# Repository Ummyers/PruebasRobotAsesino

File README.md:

## PruebasRobotAsesino
El repositorio es para las pruebas del programa final para la competencia de minisumo.

Se esta usando MSP-EXP430G2553 de la fabrica Texas Instruments

Asi como los siguientes componentes: 

1. Un regulador LD33V que convierte 5V a 3.3V el cual usa un condensador #104 (100 nanofaradios) que se conecta entre la entrada del voltaje y GND, un condensador de 10 microfaradios que va de la salida del voltaje a GND. 

2. Un regulador L7805CV que convierte 12V a 5V el cual usa un condensador #104 que va entre la salida y GND, un condensador #334 que es de 330 nanofaradios que se conecta con GND y la entrada de voltaje. 

3. Para controlar los motores usamos un driver L293D, con los pines especificados de la siguiente manera:
   Pines de entrada 2,7,15,10.\\
   Pines de salida 3,6,14,11.
ETC...

Algunas especificaciones del MSP:

El pin 1 es VCC que debe recibir a lo mas 3.3 Volts del pin 1 al 16 va un condensador de 1 nanoFaradio, del pin 16 al 20, una resistencia de 47K.

La fuente inicialmente era de 12V usamos los reguladores para obtener 5 y 3.3 volts.

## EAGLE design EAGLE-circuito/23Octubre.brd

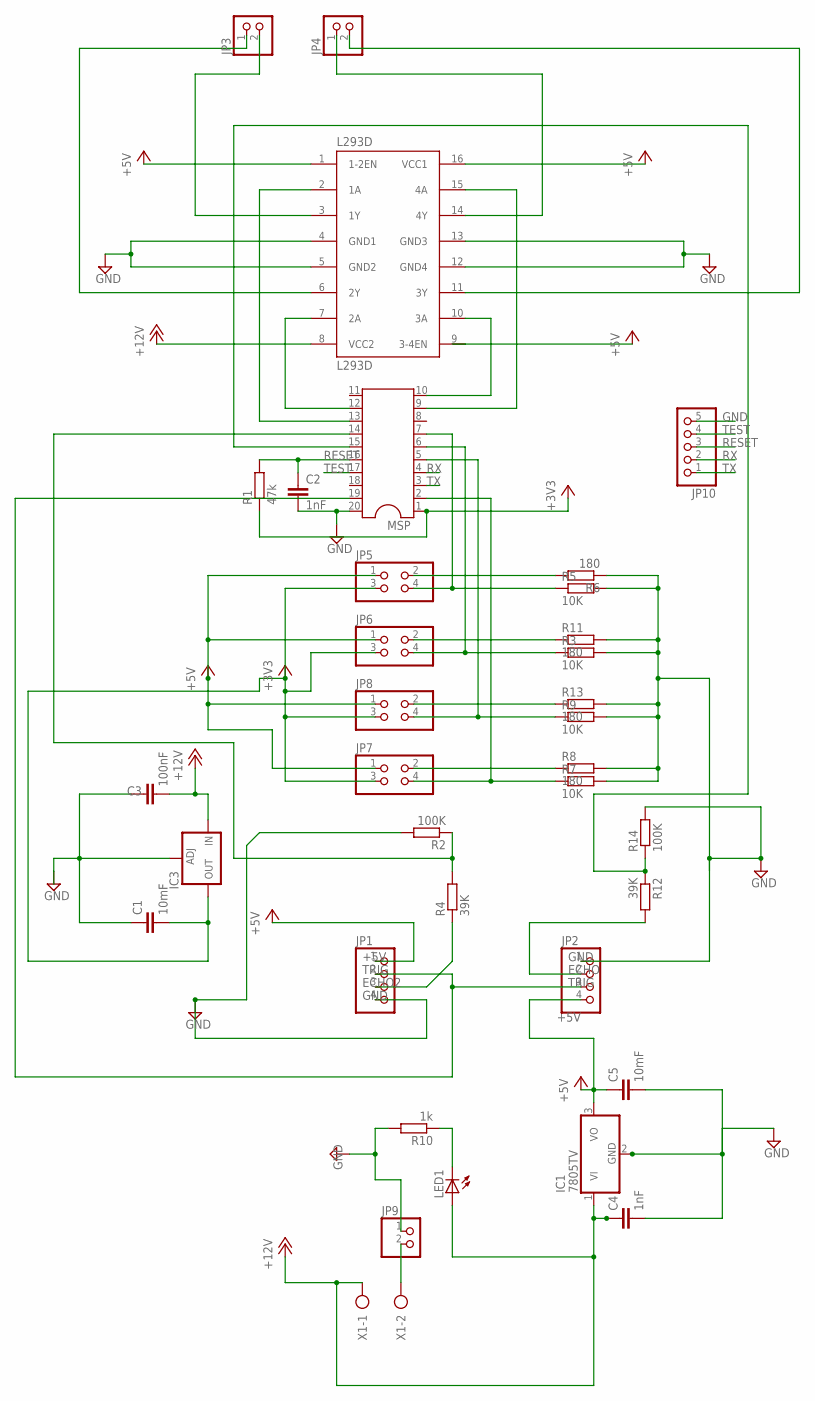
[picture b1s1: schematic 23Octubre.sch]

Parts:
C1, C5: 10mF; C050-025X075
C2, C4: 1nF; C050-025X075
C3: 100nF; C050-025X075
IC1: 7805TV; TO220V
IC3: LM317TS; 317TS
JP1, JP2: PINHD-1X4; 1X04
JP3, JP4, JP9: PINHD-1X2; 1X02
JP5, JP6, JP7, JP8: PINHD-2X2; 2X02
JP10: PINHD-1X5; 1X05
L293D: L293D; DIL16
LED1: LED5MM
MSP: DIL20
R1: 47k; 0207/10
R2, R14: 100K; 0207/10
R3, R5, R7, R9: 10K; 0207/10
R4, R12: 39K; 0207/10
R6, R8, R11, R13: 180; 0207/10
R10: 1k; 0207/10
X1: AK300/2

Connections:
+3V3: C1.2, IC3.2 (OUT), JP5.3, JP6.3, JP7.3, JP8.3, MSP.1, R1.1
+5V: C5.1, IC1.3 (VO), JP1.1, JP2.4, JP5.1, JP6.1, JP7.1, JP8.1, L293D.1 (1-2EN), L293D.9 (3-4EN), L293D.16 (VCC1)
+12V: C3.2, C4.1, IC1.1 (VI), IC3.3 (IN), L293D.8 (VCC2), LED1.A, X1.1
ECHO: JP2.2, R12.2
ECHO2: JP1.3, R4.1
GND: C1.1, C2.2, C3.1, C4.2, C5.2, IC1.2 (GND), IC3.1 (ADJ), JP1.4, JP2.1, JP9.1, JP10.5, L293D.4 (GND1), L293D.5 (GND2), L293D.12 (GND4), L293D.13 (GND3), MSP.20, R2.2, R3.2, R5.2, R6.1, R7.2, R8.2, R9.2, R10.2, R11.2, R13.2, R14.2
unnamed: L293D.7 (2A), MSP.12
unnamed: L293D.10 (3A), MSP.10
unnamed: L293D.15 (4A), MSP.9
unnamed: L293D.2 (1A), MSP.13
unnamed: JP5.4, MSP.7, R5.1
unnamed: JP6.4, MSP.6, R3.1
unnamed: JP8.4, MSP.5, R9.1
unnamed: JP7.4, MSP.2, R7.1
unnamed: JP3.1, L293D.6 (2Y)
unnamed: JP5.2, R6.2
unnamed: JP6.2, R11.1
unnamed: JP8.2, R13.1
unnamed: JP7.2, R8.1
unnamed: JP3.2, L293D.3 (1Y)
unnamed: MSP.15, R12.1, R14.1
unnamed: LED1.K (C), R10.1
unnamed: JP4.2, L293D.11 (3Y)
unnamed: JP4.1, L293D.14 (4Y)
unnamed: JP9.2, X1.2
unnamed: MSP.14, R2.1, R4.2
RESET: C2.1, JP10.3, MSP.16, R1.2
RX: JP10.2, MSP.4
TEST: JP10.4, MSP.17
TRIG: JP1.2, JP2.3, MSP.19
TX: JP10.1, MSP.3

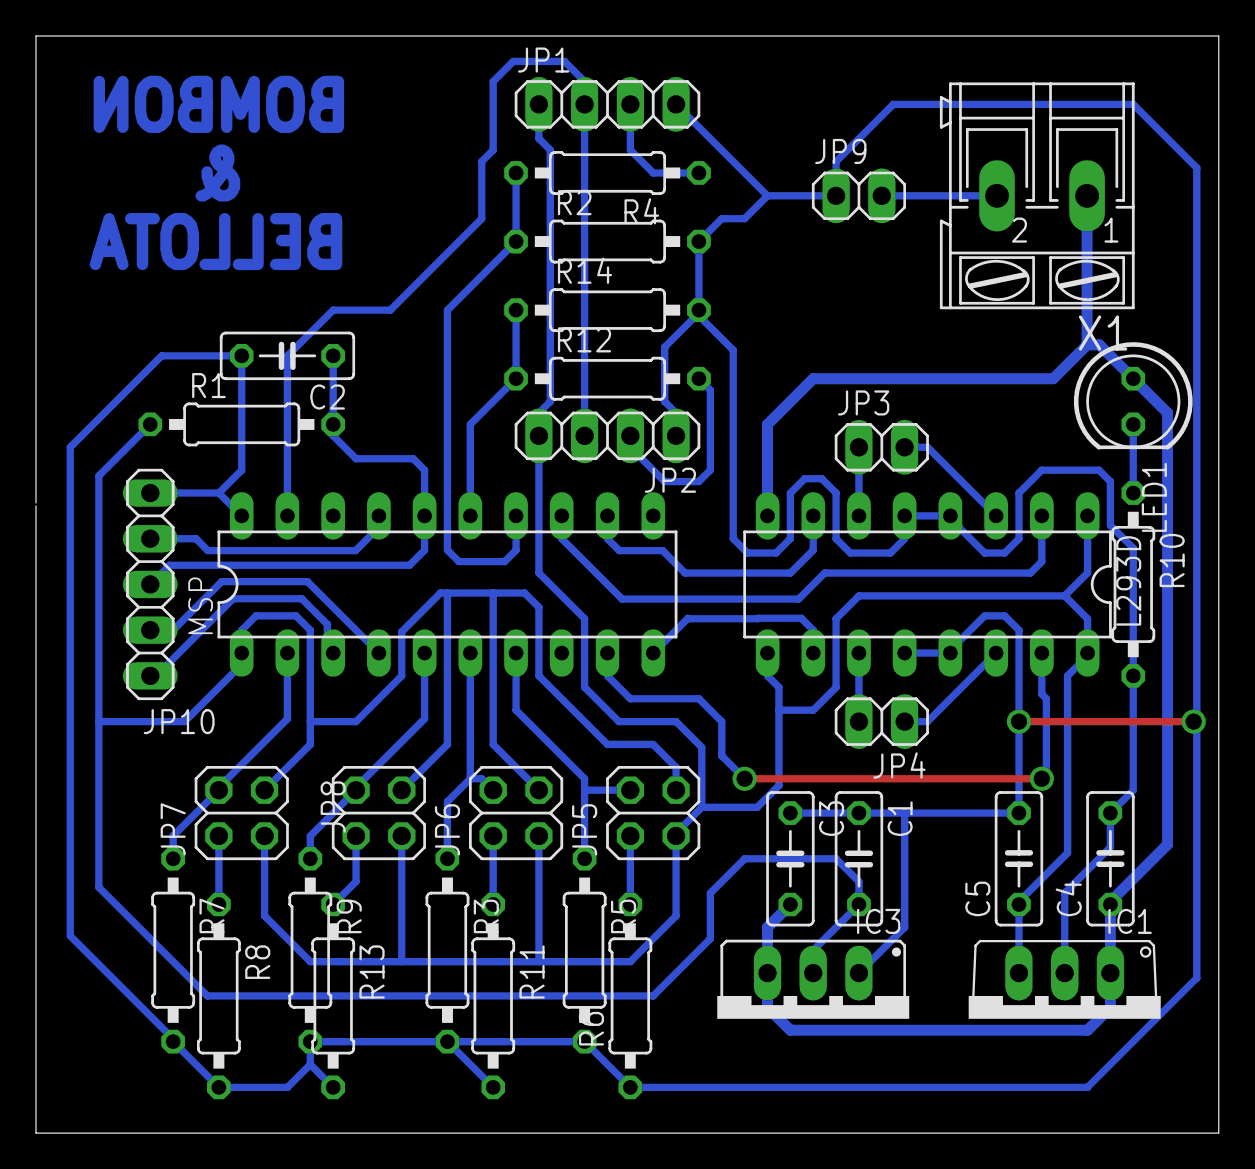
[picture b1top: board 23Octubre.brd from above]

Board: 2 copper layers, 65.7 x 61.0 mm, 35 parts (0 on the bottom side), 31 nets.

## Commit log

2018-11-08 Pruebas de vuelo segundo dia
    Pruebas del primer día y segundo día, se calibro la velocidad de los motores.
2018-11-08 Pruebas sin terminar
2018-11-10 Update _8NovPrueba1/_8NovPrueba1.ino
    Se borro el ultimo digitalWrite del metodo iniciarTrigger por que la variable tiempo nos devolvia 0, pero el problema fue que había una pista discontinua en el circuito impreso
2018-11-11 Mueve motores
    Atrás, adelante, giro.
2018-11-11 Base de datos
    Para ver archivos
2018-11-12 Eagle archivos
    Se agregan los archivos de eagle, circuito impreso
2018-11-13 Nosekestapasandaa
2018-11-15 Se agrego el delay
    Se agrego el delay para el inicio de la competencia sin embargo no se pudieron hacer las pruebas necesarias por un regulador.
2018-11-15 Documentación actualizada
2018-11-15 Orden actualizado
2018-11-18 Empuja un objeto cuando lo tiene cerca
2018-11-21 Agregando PDF
2018-11-23 Un buen de pruebas
2018-11-23 DELETE
2018-11-28 PAra que el sketch sirva
2018-11-28 actualizaciones de la semana pasada
2018-11-28 Pruebas nuevas
2018-11-28 Imagenes del circuito EAGLE
2018-11-29 15HRS antes de la competencia
2018-11-29 Se agrega versión FINAL JARVIS
2018-11-29 Versión 3:36
2018-12-03 Actualizacion de tiempo
2018-12-03 Se agregan los DataSheet
